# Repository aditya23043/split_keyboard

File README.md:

<pre>
This project is licensed under the GNU General Public License v3 (GPL-3.0).

Original Authors:
Aditya Gautam

Contributors:
-

For more information, see the LICENSE file and the GNU General Public License v3.
</pre>

# Split Ergonomic 20 Key Keyboard
> NOTE: This project is still a work in progress

<br><br><br><br>

## MOTIVE
- To design a HID (human interface device) which resembles a generic qwerty keyboard's functionality in the way that the user has to press buttons in order to get keypresses on the system connected to the keyboard.
- The differentiating factor I was hoping to get was the decrease in finger movement while typing through the use of combos and layers in order to improve the overall ergonomics in typing.
- I had observerd various other ergonomic split keyboard designs on [YouTube](https://youtube.com) and [Reddit](https://reddit.com), however, mostly none of those designs were kind of in the intersection of a generic keyboard and an ergonomic keyboard.
- Hence, I came to the conclusion to design my own split ergonomic keyboard.

## LOGS

### Inspiration

- [This](https://youtu.be/wTMcH7u-vu0?feature=shared) video by [Josean Martinez](https://www.youtube.com/@joseanmartinez) popped up on my YouTube feed one day and got me thinking about split ergonomic keyboards
- After further research, I came across these two wonderful channels that helped me to design my own PCB for the keyboard
    1. [Ben Vallack](https://www.youtube.com/@BenVallack)
    2. [Joe Scotto](https://www.youtube.com/@joe_scotto)

### Keyboard Designing

- I followed [Joe Scotto's](https://www.youtube.com/@joe_scotto) [video](https://youtu.be/8WXpGTIbxlQ?feature=shared) tutorial on how to design PCB using KiCad and ordered the PCB through [Robu.in](https://robu.in)
- Gerber File: [Gerber](reversible_20_gerber.zip)
- PCB: 

<br><br><br><br>

### Assembly ([ASSEMBLY VIDEO](https://youtu.be/sDFPSLh6BhQ?feature=shared))

<br><br><br><br>
<br><br><br><br>
<br><br><br><br>
<br><br><br><br>
- Me thinking of adding the SSD1306 oled 0.9 inch display but that idea quickly vanished since I had not planned earlier about the connectivity of the two halves, whether they will be wired or wireless and other stuff like that.

<br><br><br><br>
- After soldering the kailh hotswap sockets, I noticed that I had soldered half of them in the opposite direction which blocked the hole in which the switch was supposed to sit flush to the PCB.

<br><br><br><br>
<br><br><br><br>
- A lot of progress in between the previous image and this image.

    1. I soldered male to male header pins at the bottom of the right half so that I could connect jumper wires between the two halves and since I was using a single mcu, I directly assigned the left 10 switches to 10 gpio pins on the mcu on the right side

    2. My cheap tenting solution was to put this tommy hilfiger tie combo box (which was further vandalised by me because i wanted to test out this 20 key layout using push buttons before ordering the PCB) in between the two halves in order to achieve the perfect tilt angle

    3. But the current state of the keyboard wasn't doing it for me since I had not properly soldered the header pins and some edge pins were disconnecting. Hence, I went down the wireless route.

- And this was the layout I was using when both the halves were connected : [Layout](https://aditya23043.github.io/kb_layout/)

<br><br><br><br>
<br><br><br><br>
<br><br><br><br>

- Me trying to figure out how to make the layout work when both halves are connected independently to the system

<br><br><br><br>
<br><br><br><br>

- Left Half (Current state as of 25th July, 2024 - 11:30PM)

<br><br><br><br>
<br><br><br><br>
<br><br><br><br>

- Right Half (Current state as of 25th July, 2024 - 11:30PM)

<br><br><br><br>
<br><br><br><br>
<br><br><br><br>

### PROBLEMS

- Since this was my first custom PCB design, I ordered the first prototype I designed without further testing and thinking, and hence, I am facing problems at the assembly stage regarding core functionalities of the keyboard.
- Starting out, after the main assembly, I was still conflicted in context of connectivity.
- Initially, I started out by connecting both the halves
- As of 27th July, 10:30PM, I am still confused if I want to have a wired board or wireless or semi wireless (the halves are wired up but as a whole they are wirelessly connected to the PC)

### Nearing to Completion
- I figured, with my current knowledge alongside my research, I am unable to make both the halves of the keyboard to interact with each other wirelessly ALONGSIDE making them communicate with the system (PC/Laptop/etc..) at the same time  (as of 21/08/24 11:20PM)
- So, I figured I should connect both the halves through wires
- At the current state, both the halves are connected through 3.5mm TRRS cable
- Both the halves communicate through I2C (Inter-Integrated Circuit) protocol
- As of today, both the halves are connected to the system (PC/laptop/etc..) for power and data (sending keypresses) but once the code is finalized I am thinking of making them wirelessly connect to the system through BLE (bluetooth low energy)
- Also, as of today, I have implemented the same layout I used before : [Layout](https://aditya23043.github.io/kb_layout/) but I have not implemented the system layer yet

#### Hotswappable Switches Issue
- The switches I bought (HMX Hyacinth V2U) were a little bit loose when I put them in and out of the hotswappable socket and hence wanted to try other switches if they would stay stuck to the PCB
- I had desoldered Otemu red switches from my other 60% qwerty keyboard
- Those switches had a little bit of metal left in the pins while desoldering
- So, when I put those switches, they were perfect in fit however they made my hotswappable sockets's holes a little bit bigger and now the HMX switches would not stick to the PCB at all. Even a little bit of force would make them fall over from the PCB
- To combat this, I designed this case [./prototype_1/case/switch_plate.stl](./prototype_1/case/switch_plate.stl) for the switches to mount to

<br><br><br><br>
<br><br><br><br>
<br><br><br><br>
<br><br><br><br>
<br><br><br><br>
<br><br><br><br>

<hr>

## PROTOTYPE VER 2.0
- It has been some time since the last commit
- Finished with the 1st prototype
    - In which I had connected both the halves through wire (I2C) and each of the halves were then connected through USB to the system
- But due to two mcus and constant data travel, it was a more power consuming contraption
- And due to the wires, it was a messy prototype
- So, for this version I "was" ....
- (yes, "was" because turns out im not that great at thinking ahead of time and documenting it in real time)
- ... thinking of making both the havles be kept closer to each other and i connect both of them using wire again but not any special protocol to send data from one mcu to another
- Instead, I'll directly connect all the 10 switched (+1 ground) to the one mcu on one half just like i did in the starting stages of the prototype 1 but less flimsy because I'll be using a proper 3d printed case.
- So, only one mcu required with no special communication => so less power consumption => longer lasting in terms of battery life => happy end user => YAY
- Also, all the parts where files were mentioned are now moved to `/prototype_1/`

### CASE
- No changes in the PCB
- I will be placing both the PCBs inside one case which makes them a mono-board keyboard functionally so that the wiring doesn't go haywire when actually using the board and also so that I can hide all the messy connections (if any added afterwards) inside the case
    - Trust me, you do not want to solder 1m of single core copper wire you ordered from amazon and think that it will be portable and perfectly find and won't definitely short the whole board
- The case comprises of two parts: Switch mount plate + bottom plate
- And both the parts are held together by M3x6mm countersunk Phillips screws which will be screwed into M3x6mm brass inserts which will be pushed into the switch mount plate using a soldering iron
- I bought the screws and inserts from https://onlyscrews.in for very cheap as compared to https://amazon.in

> NOTE: Gerber viewer of kicad was a very helpful tool whose measurement tool I used extensively to measure out the distances of different components on my PCB to make a near accurate estimate for my case

### [Switch Mount Plate](./prototype_2/mount_plate.stl)
- The main structure of the case
- Consists of mount plate + boundary for the case
<br><br><br><br>
<br><br><br><br>

### [Bottom Plate](./prototype_2/bottom_plate.stl)
- Covers the case from the bottom
- Will have the rubber feet stuck to the bottom for better grip on smooth surfaces
- Is 3mm in height cus why not? (besides the fact that it will cost more)
- Has standoffs so that the PCB can rest on those
- The cylindrical standoffs with different top and bottom radii are fine in context of 3d designing but I am not quite sure about the other cuboidal standoffs since they do not seem to have good structural integrity
<br><br><br><br>
<br><br><br><br>
<br><br><br><br>

> I am yet to order these 2 parts because I am conflicted between ordering these from https://robu.in which will take more time and cost as compared to using my college's 3d printer which will be available after 29th October, 2024 (today is 18th october btw)\
> I'll probably wait since just one 1.5mm switch mount plate (just the plate not the boundaries) in my ver 1.0 costed me about 200rs per half (~2.5$)\
> And both of the above with the minimal configuration (like 15% infill, standard nozzle, black ABS) is showing me about ~1500rs (~18$)

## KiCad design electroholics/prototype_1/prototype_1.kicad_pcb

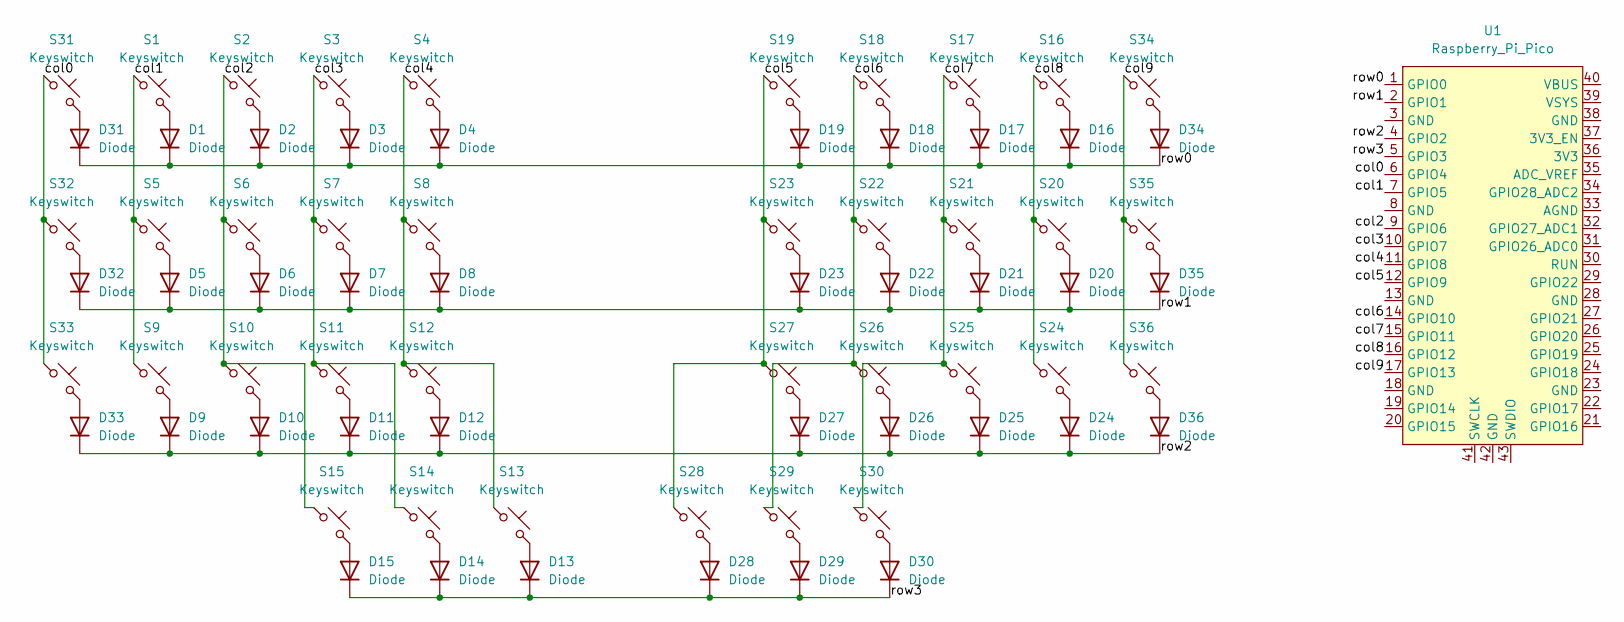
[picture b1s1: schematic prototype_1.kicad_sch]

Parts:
D1, D2, D3, D4, D5, D6, D7, D8, D9, D10, D11, D12, D13, D14, D15, D16, D17, D18, D19, D20, D21, D22, D23, D24, D25, D26, D27, D28, D29, D30, D31, D32, D33, D34, D35, D36: Diode; Diode_DO-35
S1, S2, S3, S4, S5, S6, S7, S8, S9, S10, S11, S12, S13, S14, S15, S16, S17, S18, S19, S20, S21, S22, S23, S24, S25, S26, S27, S28, S29, S30, S31, S32, S33, S34, S35, S36: Keyswitch; MX_PCB_1.00u
U1: Raspberry_Pi_Pico

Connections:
/col0: S31.1, S32.1, S33.1, U1.6 (GPIO4)
/col1: S1.1, S5.1, S9.1, U1.7 (GPIO5)
/col2: S2.1, S6.1, S10.1, S15.1, U1.9 (GPIO6)
/col3: S3.1, S7.1, S11.1, S14.1, U1.10 (GPIO7)
/col4: S4.1, S8.1, S12.1, S13.1, U1.11 (GPIO8)
/col5: S19.1, S23.1, S27.1, S28.1, U1.12 (GPIO9)
/col6: S18.1, S22.1, S26.1, S29.1, U1.14 (GPIO10)
/col7: S17.1, S21.1, S25.1, S30.1, U1.15 (GPIO11)
/col8: S16.1, S20.1, S24.1, U1.16 (GPIO12)
/col9: S34.1, S35.1, S36.1, U1.17 (GPIO13)
/row0: D1.1 (K), D2.1 (K), D3.1 (K), D4.1 (K), D16.1 (K), D17.1 (K), D18.1 (K), D19.1 (K), D31.1 (K), D34.1 (K), U1.1 (GPIO0)
/row1: D5.1 (K), D6.1 (K), D7.1 (K), D8.1 (K), D20.1 (K), D21.1 (K), D22.1 (K), D23.1 (K), D32.1 (K), D35.1 (K), U1.2 (GPIO1)
/row2: D9.1 (K), D10.1 (K), D11.1 (K), D12.1 (K), D24.1 (K), D25.1 (K), D26.1 (K), D27.1 (K), D33.1 (K), D36.1 (K), U1.4 (GPIO2)
/row3: D13.1 (K), D14.1 (K), D15.1 (K), D28.1 (K), D29.1 (K), D30.1 (K), U1.5 (GPIO3)
unnamed: D1.2 (A), S1.2
unnamed: D2.2 (A), S2.2
unnamed: D3.2 (A), S3.2
unnamed: D4.2 (A), S4.2
unnamed: D5.2 (A), S5.2
unnamed: D6.2 (A), S6.2
unnamed: D7.2 (A), S7.2
unnamed: D8.2 (A), S8.2
unnamed: D9.2 (A), S9.2
unnamed: D10.2 (A), S10.2
unnamed: D11.2 (A), S11.2
unnamed: D12.2 (A), S12.2
unnamed: D13.2 (A), S13.2
unnamed: D14.2 (A), S14.2
unnamed: D15.2 (A), S15.2
unnamed: D16.2 (A), S16.2
unnamed: D17.2 (A), S17.2
unnamed: D18.2 (A), S18.2
unnamed: D19.2 (A), S19.2
unnamed: D20.2 (A), S20.2
unnamed: D21.2 (A), S21.2
unnamed: D22.2 (A), S22.2
unnamed: D23.2 (A), S23.2
unnamed: D24.2 (A), S24.2
unnamed: D25.2 (A), S25.2
unnamed: D26.2 (A), S26.2
unnamed: D27.2 (A), S27.2
unnamed: D28.2 (A), S28.2
unnamed: D29.2 (A), S29.2
unnamed: D30.2 (A), S30.2
unnamed: D31.2 (A), S31.2
unnamed: D32.2 (A), S32.2
unnamed: D33.2 (A), S33.2
unnamed: D34.2 (A), S34.2
unnamed: D35.2 (A), S35.2
unnamed: D36.2 (A), S36.2

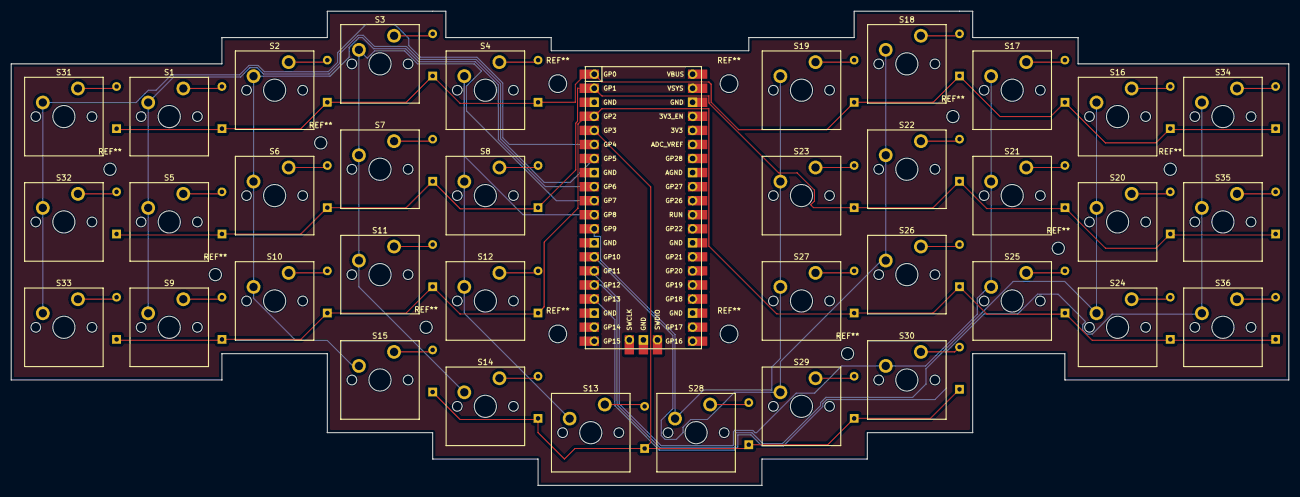
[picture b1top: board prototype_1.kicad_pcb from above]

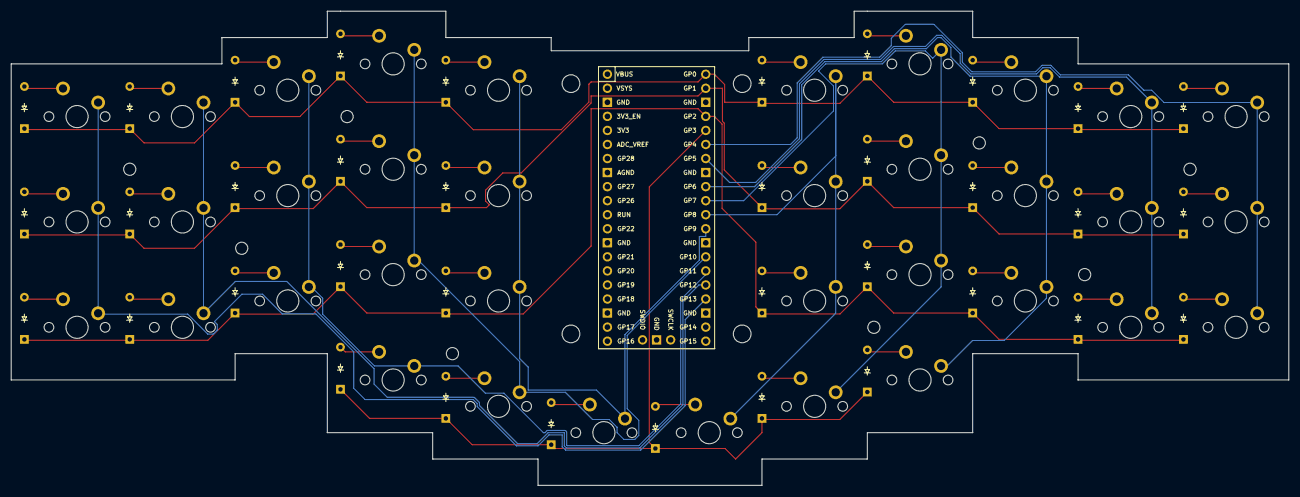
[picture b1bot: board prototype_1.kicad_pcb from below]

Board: 2 copper layers, 231.0 x 85.7 mm, 73 parts (36 on the bottom side), 50 nets.

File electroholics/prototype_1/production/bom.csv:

Designator,Footprint,Quantity,Value,LCSC Part #
"D1, D10, D11, D12, D13, D14, D15, D16, D17, D18, D19, D2, D20, D21, D22, D23, D24, D25, D26, D27, D28, D29, D3, D30, D31, D32, D33, D34, D35, D36, D4, D5, D6, D7, D8, D9",Diode_DO-35,36,Diode,
"S1, S10, S11, S12, S13, S14, S15, S16, S17, S18, S19, S2, S20, S21, S22, S23, S24, S25, S26, S27, S28, S29, S3, S30, S31, S32, S33, S34, S35, S36, S4, S5, S6, S7, S8, S9",MX_PCB_1.00u,36,Keyswitch,
U1,Raspberry_Pi_Pico,1,Raspberry_Pi_Pico,

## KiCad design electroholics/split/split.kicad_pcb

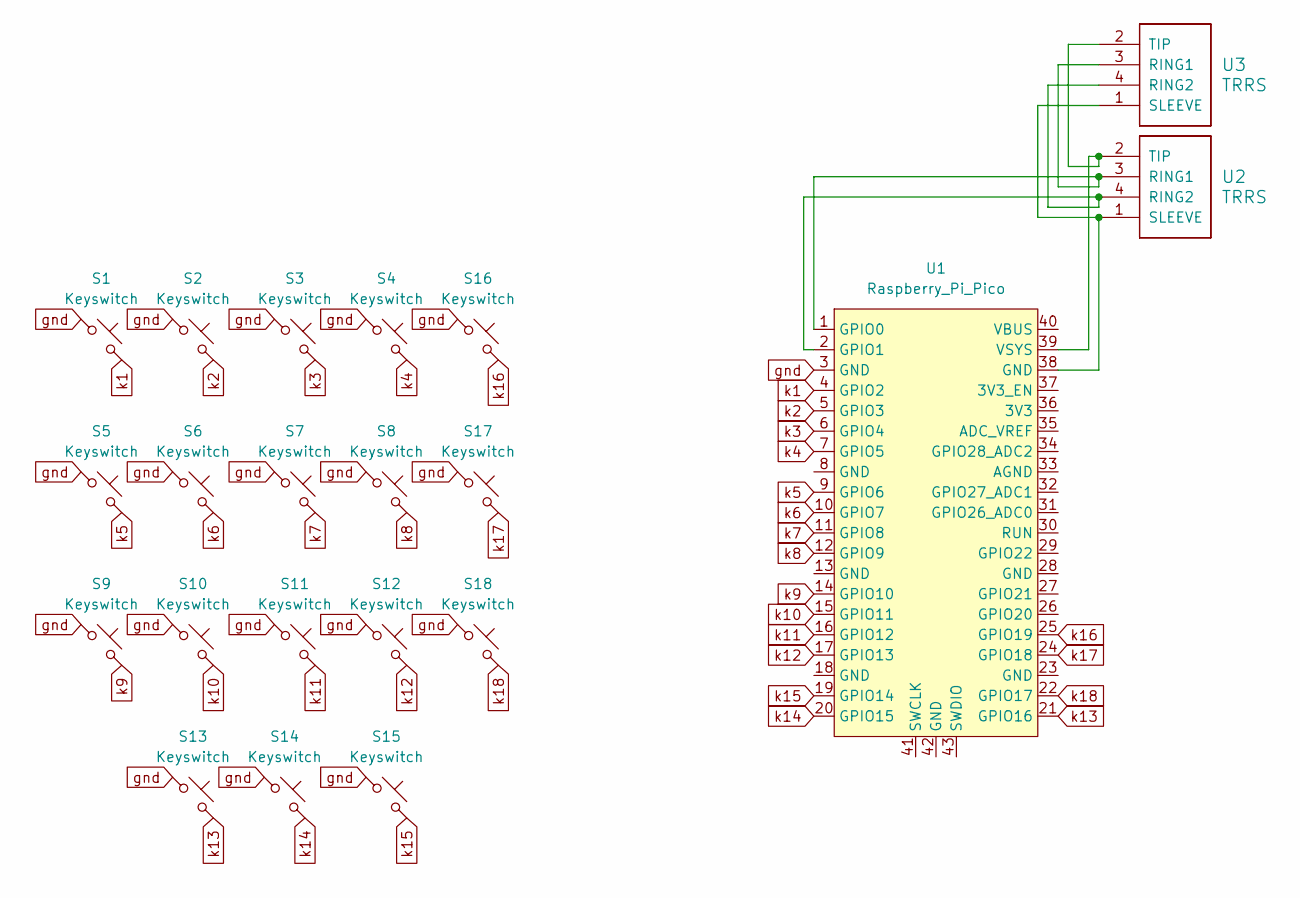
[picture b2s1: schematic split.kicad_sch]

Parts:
S1, S2, S3, S4, S5, S6, S7, S8, S9, S10, S11, S12, S13, S14, S15, S16, S17, S18: Keyswitch; MX_PCB_1.00u_Reversable
U1: Raspberry_Pi_Pico
U2, U3: TRRS; TRRS-PJ-320D

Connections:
unnamed: U1.1 (GPIO0), U2.3 (RING1), U3.3 (RING1)
unnamed: U1.2 (GPIO1), U2.4 (RING2), U3.4 (RING2)
unnamed: U1.39 (VSYS), U2.2 (TIP), U3.2 (TIP)
unnamed: U1.38 (GND), U2.1 (SLEEVE), U3.1 (SLEEVE)
gnd: S1.1, S2.1, S3.1, S4.1, S5.1, S6.1, S7.1, S8.1, S9.1, S10.1, S11.1, S12.1, S13.1, S14.1, S15.1, S16.1, S17.1, S18.1, U1.3 (GND)
k1: S1.2, U1.4 (GPIO2)
k2: S2.2, U1.5 (GPIO3)
k3: S3.2, U1.6 (GPIO4)
k4: S4.2, U1.7 (GPIO5)
k5: S5.2, U1.9 (GPIO6)
k6: S6.2, U1.10 (GPIO7)
k7: S7.2, U1.11 (GPIO8)
k8: S8.2, U1.12 (GPIO9)
k9: S9.2, U1.14 (GPIO10)
k10: S10.2, U1.15 (GPIO11)
k11: S11.2, U1.16 (GPIO12)
k12: S12.2, U1.17 (GPIO13)
k13: S13.2, U1.21 (GPIO16)
k14: S14.2, U1.20 (GPIO15)
k15: S15.2, U1.19 (GPIO14)
k16: S16.2, U1.25 (GPIO19)
k17: S17.2, U1.24 (GPIO18)
k18: S18.2, U1.22 (GPIO17)

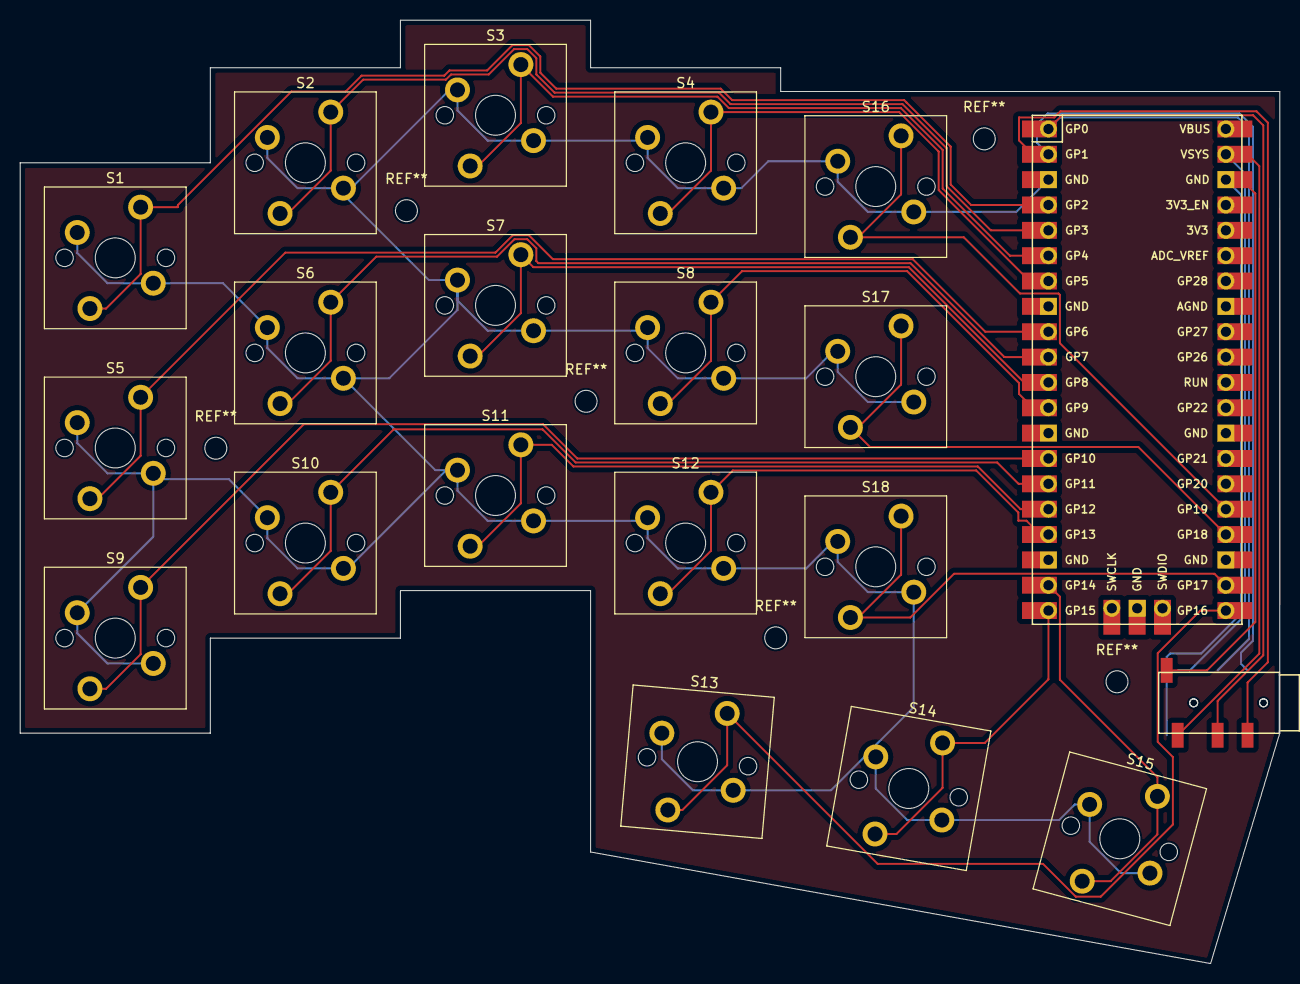
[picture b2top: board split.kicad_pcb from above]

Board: 2 copper layers, 126.2 x 94.5 mm, 21 parts (1 on the bottom side), 23 nets.

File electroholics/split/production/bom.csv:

Designator,Footprint,Quantity,Value,LCSC Part #
"S1, S10, S11, S12, S13, S14, S15, S16, S17, S18, S2, S3, S4, S5, S6, S7, S8, S9",MX_PCB_1.00u_Reversable,18,Keyswitch,
U1,Raspberry_Pi_Pico,1,Raspberry_Pi_Pico,
"U2, U3",TRRS-PJ-320D,2,TRRS,

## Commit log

2024-08-21 Create LICENSE
2024-10-14 prototype 2 begins
2024-10-14 some minor changes in the readme
2024-10-14 switch mount plate hopefully done
2024-10-14 Added hole to pass wires between left and right halves
2024-10-18 prototype ver 2.0 has begun
2024-10-18 fixed readme
2024-10-18 updated the STLs
2024-10-18 updated links
2024-10-18 finally links working now
2024-11-03 trying to make a case for handwired dactyl
2024-12-02 new ideas
2024-12-25 free pcb from electroholics yoo
2025-01-17 removed large file
